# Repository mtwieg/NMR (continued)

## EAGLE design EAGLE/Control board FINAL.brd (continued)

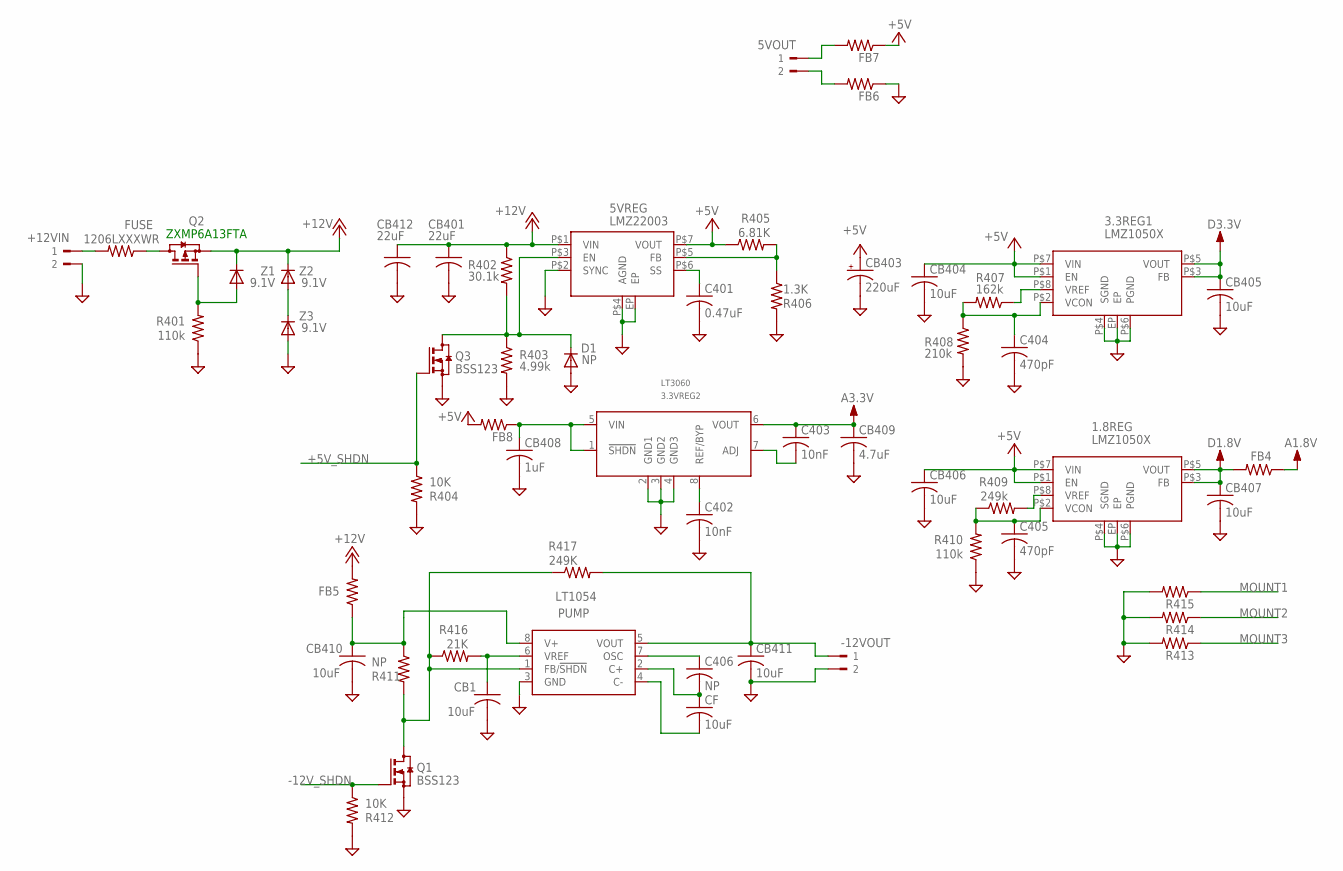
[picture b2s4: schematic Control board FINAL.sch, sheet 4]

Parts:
1.8REG, 3.3REG1: LMZ1050X; LLP-8
3.3VREG2: LT3060; TSOT-8
5VOUT: TERM-2OMNIMATE_SL; OMNIMATE_SL_2POS
5VREG: LMZ22003; TO-PMOD7
+12VIN: TERM-2OMNIMATE_SL; OMNIMATE_SL_2POS
-12VOUT: TERM-2OMNIMATE_SL; OMNIMATE_SL_2POS
C401: 0.47uF; C0805
C402, C403: 10nF; C0603
C404, C405: 470pF; C0603
C406: NP; C0805
CB1, CB404, CB405, CB406, CB407, CB410, CB411: 10uF; C0805
CB401, CB412: 22uF; C1210
CB403: 220uF; E3,5-8
CB408: 1uF; C0805
CB409: 4.7uF; C0805
CF: 10uF; C0805
D1: NP; SOD323-W
FB4: R-US_R0805; R0805
FB5, FB6, FB7, FB8: R-US_R0603; R0603
FUSE: 1206LXXXWR; R1206
PUMP: LT1054; SOIC-8
Q1, Q3: BSS123; SOT23
Q2: ZXMP6A13FTA; SOT23
R401, R410: 110k; R0805
R402: 30.1k; R0805
R403: 4.99k; R0805
R404, R412: 10K; R0805
R405: 6.81K; R0805
R406: 1.3K; R0805
R407: 162k; R0805
R408: 210k; R0805
R409: 249k; R0805
R411: NP; R0805
R413, R414, R415: R-US_R0805; R0805
R416: 21K; R0805
R417: 249K; R0805
Z1: 9.1V; SOD123
Z2, Z3: 9.1V; DO214AC

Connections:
+5V: 1.8REG.P$1 (EN), 1.8REG.P$7 (VIN), 3.3REG1.P$1 (EN), 3.3REG1.P$7 (VIN), 5VREG.P$7 (VOUT), CB403.+, CB404.1, CB406.1, FB7.1, FB8.2, R405.1; also elsewhere on the board
+5V_SHDN: Q3.1 (G), R404.1; also elsewhere on the board
+12V: 5VREG.P$1 (VIN), CB401.1, CB412.1, FB5.2, Q2.2 (S), R402.1, Z1.C, Z2.C
-12V_SHDN: Q1.1 (G), R412.1; also elsewhere on the board
A1.8V: FB4.1; also elsewhere on the board
A3.3V: 3.3VREG2.6 (VOUT), C403.1, CB409.1; also elsewhere on the board
D1.8V: 1.8REG.P$3 (FB), 1.8REG.P$5 (VOUT), CB407.1, FB4.2; also elsewhere on the board
D3.3V: 3.3REG1.P$3 (FB), 3.3REG1.P$5 (VOUT), CB405.1; also elsewhere on the board
GND: 1.8REG.EP, 1.8REG.P$4 (SGND), 1.8REG.P$6 (PGND), 3.3REG1.EP, 3.3REG1.P$4 (SGND), 3.3REG1.P$6 (PGND), 3.3VREG2.2 (GND1), 3.3VREG2.3 (GND2), 3.3VREG2.4 (GND3), 5VREG.EP, 5VREG.P$2 (SYNC), 5VREG.P$4 (AGND), +12VIN.2, -12VOUT.2, C401.2, C402.2, C404.2, C405.2, CB1.2, CB401.2, CB403.-, CB404.2, CB405.2, CB406.2, CB407.2, CB408.2, CB409.2, CB410.2, CB411.2, CB412.2, D1.A, FB6.1, PUMP.3 (GND), Q1.2 (S), Q3.2 (S), R401.1, R403.2, R404.2, R406.2, R408.2, R410.1, R412.2, R413.2, R414.2, R415.2, Z3.A; also elsewhere on the board
MOUNT1: R415.1
MOUNT2: R414.1
MOUNT3: R413.1
unnamed: 5VREG.P$6 (SS), C401.1
unnamed: 5VREG.P$3 (EN), D1.C, Q3.3 (D), R402.2, R403.1
unnamed: 5VOUT.1, FB7.2
unnamed: 5VOUT.2, FB6.2
unnamed: C406.1, PUMP.7 (OSC)
unnamed: C406.2, CF.1, PUMP.2 (C+)
unnamed: 5VREG.P$5 (FB), R405.2, R406.1
unnamed: CB410.1, FB5.1, PUMP.8 (V+), R411.1
unnamed: 3.3REG1.P$2 (VCON), C404.1, R407.2, R408.1
unnamed: 3.3REG1.P$8 (VREF), R407.1
unnamed: 1.8REG.P$8 (VREF), R409.2
unnamed: 1.8REG.P$2 (VCON), C405.1, R409.1, R410.2
unnamed: CB1.1, PUMP.6 (VREF), R416.2
unnamed: 3.3VREG2.8 (REF/BYP), C402.1
unnamed: 3.3VREG2.7 (ADJ), C403.2
unnamed: +12VIN.1, FUSE.2
unnamed: Q2.1 (G), R401.2, Z1.A
unnamed: FUSE.1, Q2.3 (D)
unnamed: -12VOUT.1, CB411.1, PUMP.5 (VOUT), R417.2
unnamed: CF.2, PUMP.4 (C-)
unnamed: Z2.A, Z3.C
unnamed: 3.3VREG2.1 (!SHDN), 3.3VREG2.5 (VIN), CB408.1, FB8.1
unnamed: PUMP.1 (FB/!SHDN), Q1.3 (D), R411.2, R416.1, R417.1

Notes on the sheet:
ZXMP6A13FTA

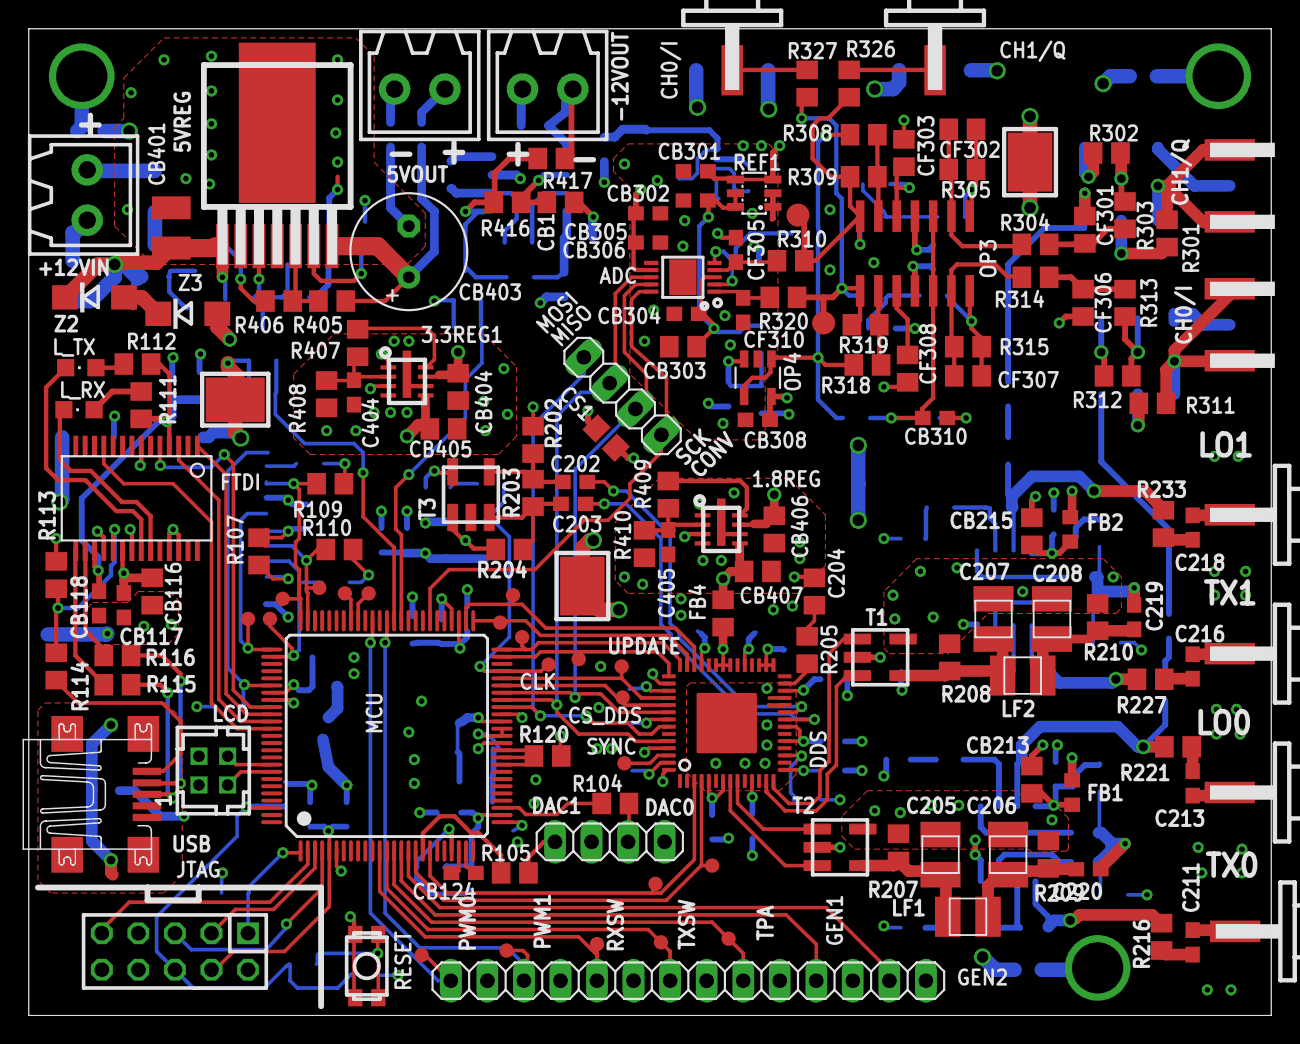
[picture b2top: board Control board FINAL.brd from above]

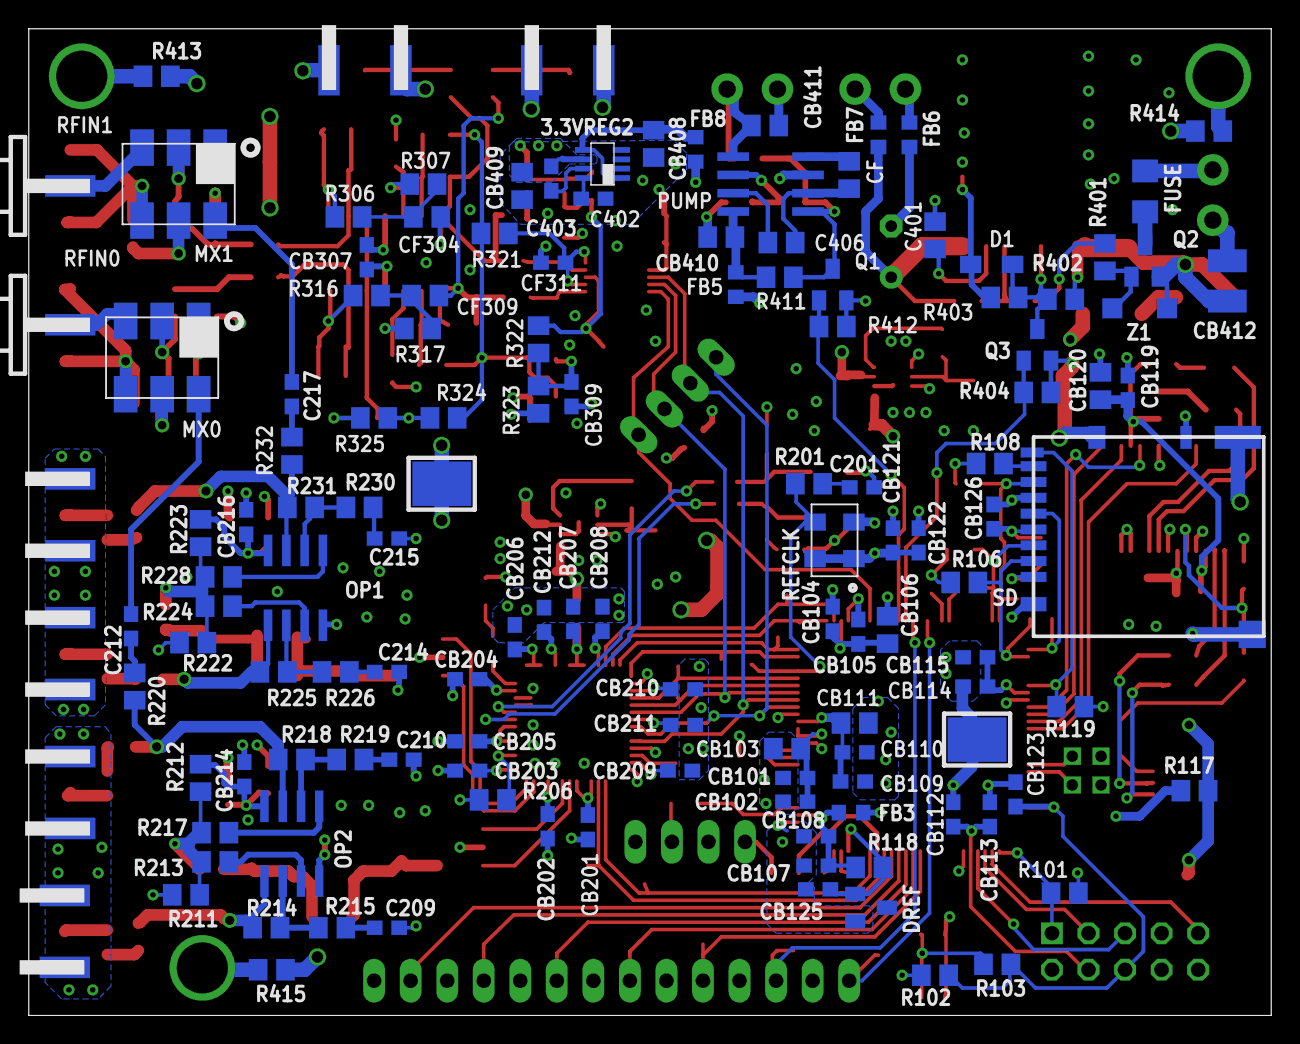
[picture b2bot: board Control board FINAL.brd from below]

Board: 4 copper layers, 86.4 x 68.6 mm, 287 parts (128 on the bottom side), 174 nets.

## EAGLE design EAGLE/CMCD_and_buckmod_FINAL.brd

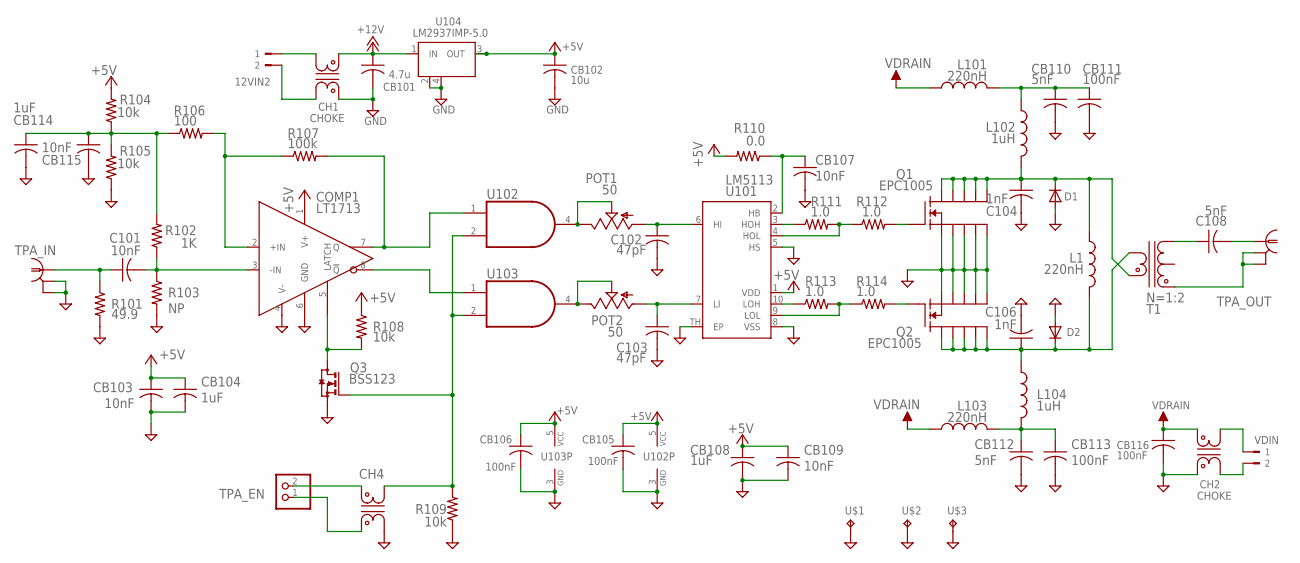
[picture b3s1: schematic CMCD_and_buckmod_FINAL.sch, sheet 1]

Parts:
12VIN2: TERM-2OMNIMATE_SL; OMNIMATE_SL_2POS
C101: 10nF; C0805
C102, C103: 47pF; C0805
C104, C106: 1nF; 1008
C108: 5nF; 1008
CB101: 4.7u; C0805
CB102: 10u; C0805
CB103, CB107, CB109, CB115: 10nF; C0603
CB104, CB108: 1uF; C0603
CB105, CB106: 100nF; C0603
CB110, CB112: 5nF; 1008
CB111, CB113, CB116: 100nF; C0805
CB114: 1uF; C0805
CH1, CH2: CHOKE; CHOKE_DLW5BT
CH4: CHOKEDLW31S; CHOKE_DLW31S
COMP1: LT1713; MSOP-8
D1, D2: DIODE-DO214AC; DO214AC
L1, L101, L103: 220nH; GENERAL-1
L102, L104: 1uH; GENERAL-1
POT1, POT2: 50; 3223W
Q1, Q2: EPC1005; 11-LGA
Q3: BSS123; SOT23
R101: 49.9; R0805
R102: 1K; R0805
R103: NP; R0805
R104, R105, R108, R109: 10k; R0805
R106: 100; R0805
R107: 100k; R0805
R110: 0.0; R0603
R111, R112, R113, R114: 1.0; R0603
T1: N=1:2; BALUN_GENERAL_BIG
TPA_EN: PINHD-1X2; 1X02
TPA_IN: BNC-EDGE
TPA_OUT: BNC-EDGE
U101: LM5113; LLP-10
U102, U103: 74AHC1G08DBV; SOT23-5
U104: LM2937IMP-5.0; SOT223
U$1, U$2, U$3: TESTPOINTKEYSTONE_ELECTRONICS_5016; SMD_TESTPAD
VDIN: TERM-2OMNIMATE_SL; OMNIMATE_SL_2POS

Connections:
+5V: CB102.1, CB103.1, CB104.1, CB105.1, CB106.1, CB108.1, CB109.1, COMP1.1 (V+), R104.2, R108.1, R110.2, U101.1 (VDD), U102.5 (VCC), U103.5 (VCC), U104.3 (OUT); also elsewhere on the board
+12V: CB101.1, CH1.P$4 (4), U104.1 (IN); also elsewhere on the board
GND: C102.2, C103.2, C104.P$2 (2), C106.P$2 (2), CB101.2, CB102.2, CB103.2, CB104.2, CB105.2, CB106.2, CB107.2, CB108.2, CB109.2, CB110.P$2 (2), CB111.2, CB112.P$2 (2), CB113.2, CB114.2, CB115.2, CB116.2, CH1.P$1 (1), CH2.P$1 (1), CH4.P$2 (2), COMP1.4 (V-), COMP1.6 (GND), D1.A, D2.A, Q1.2 (S1), Q1.4 (S2), Q1.6 (S3), Q1.8 (S4), Q1.10 (S5), Q2.2 (S1), Q2.4 (S2), Q2.6 (S3), Q2.8 (S4), Q2.10 (S5), Q3.2 (S), R101.2, R103.2, R105.1, R109.1, TPA_IN.S1 (GND1), TPA_IN.S2 (GND2), U101.5 (HS), U101.8 (VSS), U101.TH (EP), U102.3 (GND), U103.3 (GND), U104.2 (GND), U104.4 (GND), U$1.P$1, U$2.P$1, U$3.P$1; also elsewhere on the board
unnamed: R111.1, U101.3 (HOH)
unnamed: R111.2, R112.1, U101.4 (HOL)
unnamed: R113.1, U101.10 (LOH)
unnamed: R113.2, R114.1, U101.9 (LOL)
unnamed: Q2.1 (G), R114.2
unnamed: Q1.1 (G), R112.2
unnamed: CB107.1, R110.1, U101.2 (HB)
unnamed: COMP1.7 (Q), R107.2, U102.1 (I0)
unnamed: POT1.2 (S), POT1.3 (E), U102.4 (O)
unnamed: POT2.2 (S), POT2.3 (E), U103.4 (O)
unnamed: CB114.1, CB115.1, R102.2, R104.1, R105.2, R106.1
unnamed: COMP1.8 (!Q), U103.1 (I0)
unnamed: COMP1.5 (LATCH), Q3.3 (D), R108.2
unnamed: T1.S1 (6), TPA_OUT.S1 (GND1), TPA_OUT.S2 (GND2)
unnamed: C102.1, POT1.1 (A), U101.6 (HI)
unnamed: COMP1.2 (+IN), R106.2, R107.1
unnamed: C101.2, COMP1.3 (-IN), R102.1, R103.1
unnamed: C101.1, R101.1, TPA_IN.I (1)
unnamed: CH4.P$3 (3), Q3.1 (G), R109.2, U102.2 (I1), U103.2 (I1)
unnamed: CH2.P$3 (3), VDIN.1
unnamed: CH2.P$2 (2), VDIN.2
unnamed: C106.P$1 (1), D2.C, L1.P$2 (2), L104.P$1 (1), Q2.3 (D1), Q2.5 (D2), Q2.7 (D3), Q2.9 (D4), Q2.11 (D5), T1.P2 (3)
unnamed: C103.1, POT2.1 (A), U101.7 (LI)
unnamed: C104.P$1 (1), D1.C, L1.P$1 (1), L102.P$2 (2), Q1.3 (D1), Q1.5 (D2), Q1.7 (D3), Q1.9 (D4), Q1.11 (D5), T1.P1 (1)
unnamed: CB110.P$1 (1), CB111.1, L101.P$2 (2), L102.P$1 (1)
unnamed: CB112.P$1 (1), CB113.1, L103.P$2 (2), L104.P$2 (2)
unnamed: C108.P$2 (2), TPA_OUT.I (1)
unnamed: C108.P$1 (1), T1.S2 (4)
unnamed: 12VIN2.1, CH1.P$3 (3)
unnamed: 12VIN2.2, CH1.P$2 (2)
unnamed: CH4.P$4 (4), TPA_EN.2
unnamed: CH4.P$1 (1), TPA_EN.1
VDRAIN: CB116.1, CH2.P$4 (4), L101.P$1 (1), L103.P$1 (1)

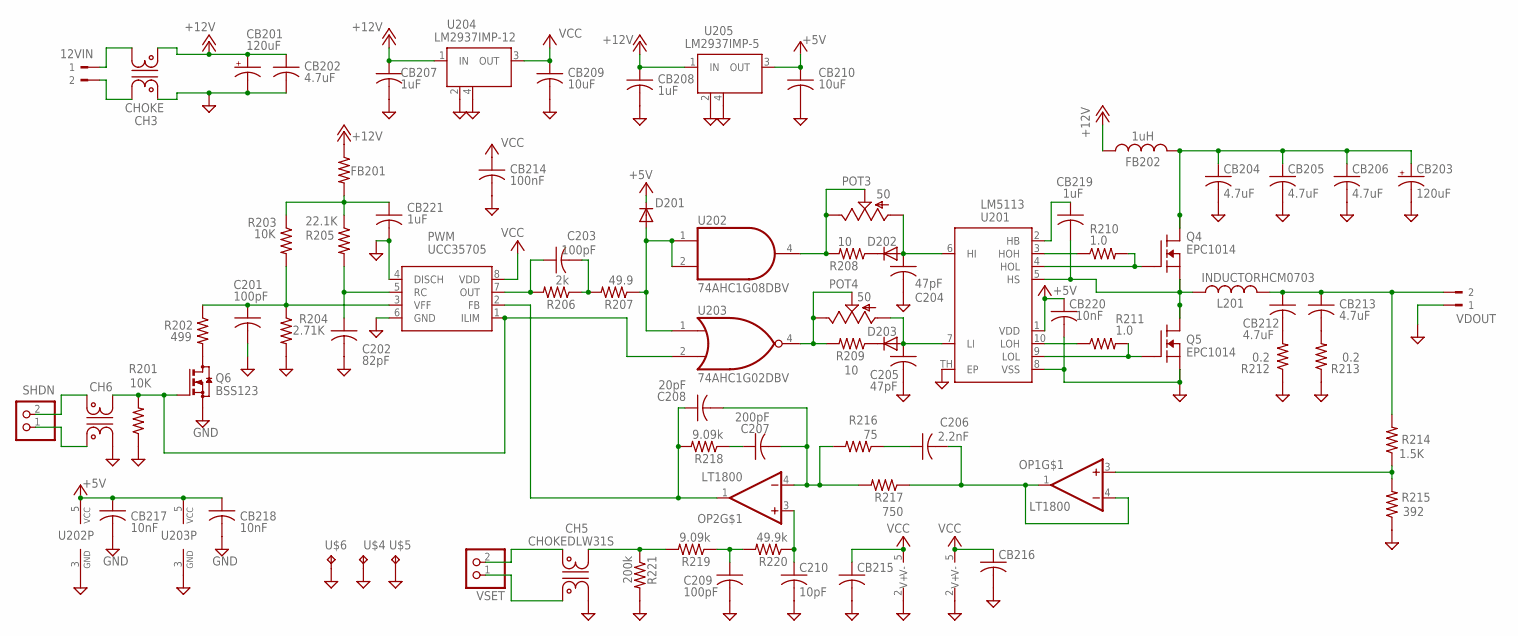
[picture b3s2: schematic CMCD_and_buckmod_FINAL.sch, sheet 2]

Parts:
12VIN: TERM-2OMNIMATE_SL; OMNIMATE_SL_2POS
C201, C203, C209: 100pF; C0805
C202: 82pF; C0805
C204, C205: 47pF; C0603
C206: 2.2nF; C0805
C207: 200pF; C0805
C208: 20pF; C0805
C210: 10pF; C0805
CB201, CB203: 120uF; E3,5-8
CB202, CB204, CB212, CB213: 4.7uF; C0805
CB205, CB206: 4.7uF; 1206-LONG
CB207, CB208, CB221: 1uF; C0805
CB209, CB210: 10uF; C0805
CB214: 100nF; C0603
CB215, CB216: C-USC0603; C0603
CB217, CB218, CB220: 10nF; C0603
CB219: 1uF; C0603
CH3: CHOKE; CHOKE_DLW5BT
CH5, CH6: CHOKEDLW31S; CHOKE_DLW31S
D201, D202, D203: DIODE-SOD323-W; SOD323-W
FB201: R-US_R0805; R0805
FB202: 1uH; 1008
L201: INDUCTORHCM0703; HCM0703
OP1, OP2: LT1800; SOT23-5
POT3, POT4: 50; 3223W
PWM: UCC35705; MSOP-8
Q4, Q5: EPC1014; 5-LGA
Q6: BSS123; SOT23
R201, R203: 10K; R0805
R202: 499; R0805
R204: 2.71K; R0805
R205: 22.1K; R0805
R206: 2k; R0805
R207: 49.9; R0805
R208, R209: 10; R0805
R210, R211: 1.0; R0603
R212, R213: 0.2; R0805
R214: 1.5K; R0805
R215: 392; R0805
R216: 75; R0805
R217: 750; R0805
R218, R219: 9.09k; R0805
R220: 49.9k; R0805
R221: 200k; R0805
SHDN: PINHD-1X2; 1X02
U201: LM5113; LLP-10
U202: 74AHC1G08DBV; SOT23-5
U203: 74AHC1G02DBV; SOT23-5
U204: LM2937IMP-12; SOT223
U205: LM2937IMP-5; SOT223
U$4, U$5, U$6: TESTPOINTKEYSTONE_ELECTRONICS_5016; SMD_TESTPAD
VDOUT: TERM-2OMNIMATE_SL; OMNIMATE_SL_2POS
VSET: PINHD-1X2; 1X02

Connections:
+5V: CB210.1, CB217.1, CB218.1, CB220.1, D201.C, U201.1 (VDD), U202.5 (VCC), U203.5 (VCC), U205.3 (OUT); also elsewhere on the board
+12V: CB201.+, CB202.1, CB207.1, CB208.1, CH3.P$4 (4), FB201.1, FB202.P$1 (1), U204.1 (IN), U205.1 (IN); also elsewhere on the board
+VIN: CB203.+, CB204.1, CB205.1, CB206.1, FB202.P$2 (2), Q4.3 (D), Q4.5 (D1)
GND: C201.2, C202.2, C204.2, C205.2, C209.2, C210.2, CB201.-, CB202.2, CB203.-, CB204.2, CB205.2, CB206.2, CB207.2, CB208.2, CB209.2, CB210.2, CB214.2, CB215.2, CB216.2, CB217.2, CB218.2, CB220.2, CB221.2, CH3.P$1 (1), CH5.P$2 (2), CH6.P$2 (2), OP1.2 (V-), OP2.2 (V-), PWM.4 (DISCH), PWM.6 (GND), Q5.2 (S1), Q5.4 (S2), Q6.2 (S), R201.1, R204.2, R212.1, R213.1, R215.1, R221.2, U201.8 (VSS), U201.TH (EP), U202.3 (GND), U203.3 (GND), U204.2 (GND), U204.4 (GND), U205.2 (GND), U205.4 (GND), U$4.P$1, U$5.P$1, U$6.P$1, VDOUT.1; also elsewhere on the board
unnamed: 12VIN.2, CH3.P$2 (2)
unnamed: 12VIN.1, CH3.P$3 (3)
unnamed: R210.1, U201.3 (HOH)
unnamed: Q4.1 (G), R210.2, U201.4 (HOL)
unnamed: CH5.P$4 (4), VSET.2
unnamed: CH5.P$1 (1), VSET.1
unnamed: CH6.P$4 (4), SHDN.2
unnamed: CH6.P$1 (1), SHDN.1
unnamed: R211.1, U201.10 (LOH)
unnamed: Q5.1 (G), R211.2, U201.9 (LOL)
unnamed: CB219.2, L201.P$1 (1), Q4.2 (S1), Q4.4 (S2), Q5.3 (D), Q5.5 (D1), U201.5 (HS)
unnamed: C205.1, D203.A, POT4.1 (A), U201.7 (LI)
unnamed: C204.1, D202.A, POT3.1 (A), U201.6 (HI)
unnamed: POT4.2 (S), POT4.3 (E), R209.2, U203.4 (O)
unnamed: CB219.1, U201.2 (HB)
unnamed: C208.1, OP2.1 (OUT), PWM.2 (FB), R218.2
unnamed: C207.2, C208.2, OP2.4 (-IN), R216.2, R217.2
unnamed: C207.1, R218.1
unnamed: C206.1, R216.1
unnamed: C206.2, OP1.1 (OUT), OP1.4 (-IN), R217.1
unnamed: CB213.2, R213.2
unnamed: CB212.1, CB213.1, L201.P$2 (2), R214.2, VDOUT.2
unnamed: OP1.3 (+IN), R214.1, R215.2
unnamed: C209.1, R219.1, R220.2
unnamed: CB212.2, R212.2
unnamed: CH5.P$3 (3), R219.2, R221.1
unnamed: D201.A, R207.1, U202.1 (I0), U202.2 (I1), U203.1 (I0)
unnamed: C202.1, PWM.5 (RC), R205.2
unnamed: C201.1, PWM.3 (VFF), R202.1, R203.2, R204.1
unnamed: C203.1, PWM.7 (OUT), R206.2
unnamed: C203.2, R206.1, R207.2
unnamed: Q6.3 (D), R202.2
unnamed: CB221.1, FB201.2, R203.1, R205.1
unnamed: D203.C, R209.1
unnamed: D202.C, R208.1
unnamed: POT3.2 (S), POT3.3 (E), R208.2, U202.4 (O)
unnamed: CH6.P$3 (3), PWM.1 (ILIM), Q6.1 (G), R201.2, U203.2 (I1)
OP2: C210.1, OP2.3 (+IN), R220.1
VCC: CB209.1, CB214.1, CB215.1, CB216.1, OP1.5 (V+), OP2.5 (V+), PWM.8 (VDD), U204.3 (OUT)

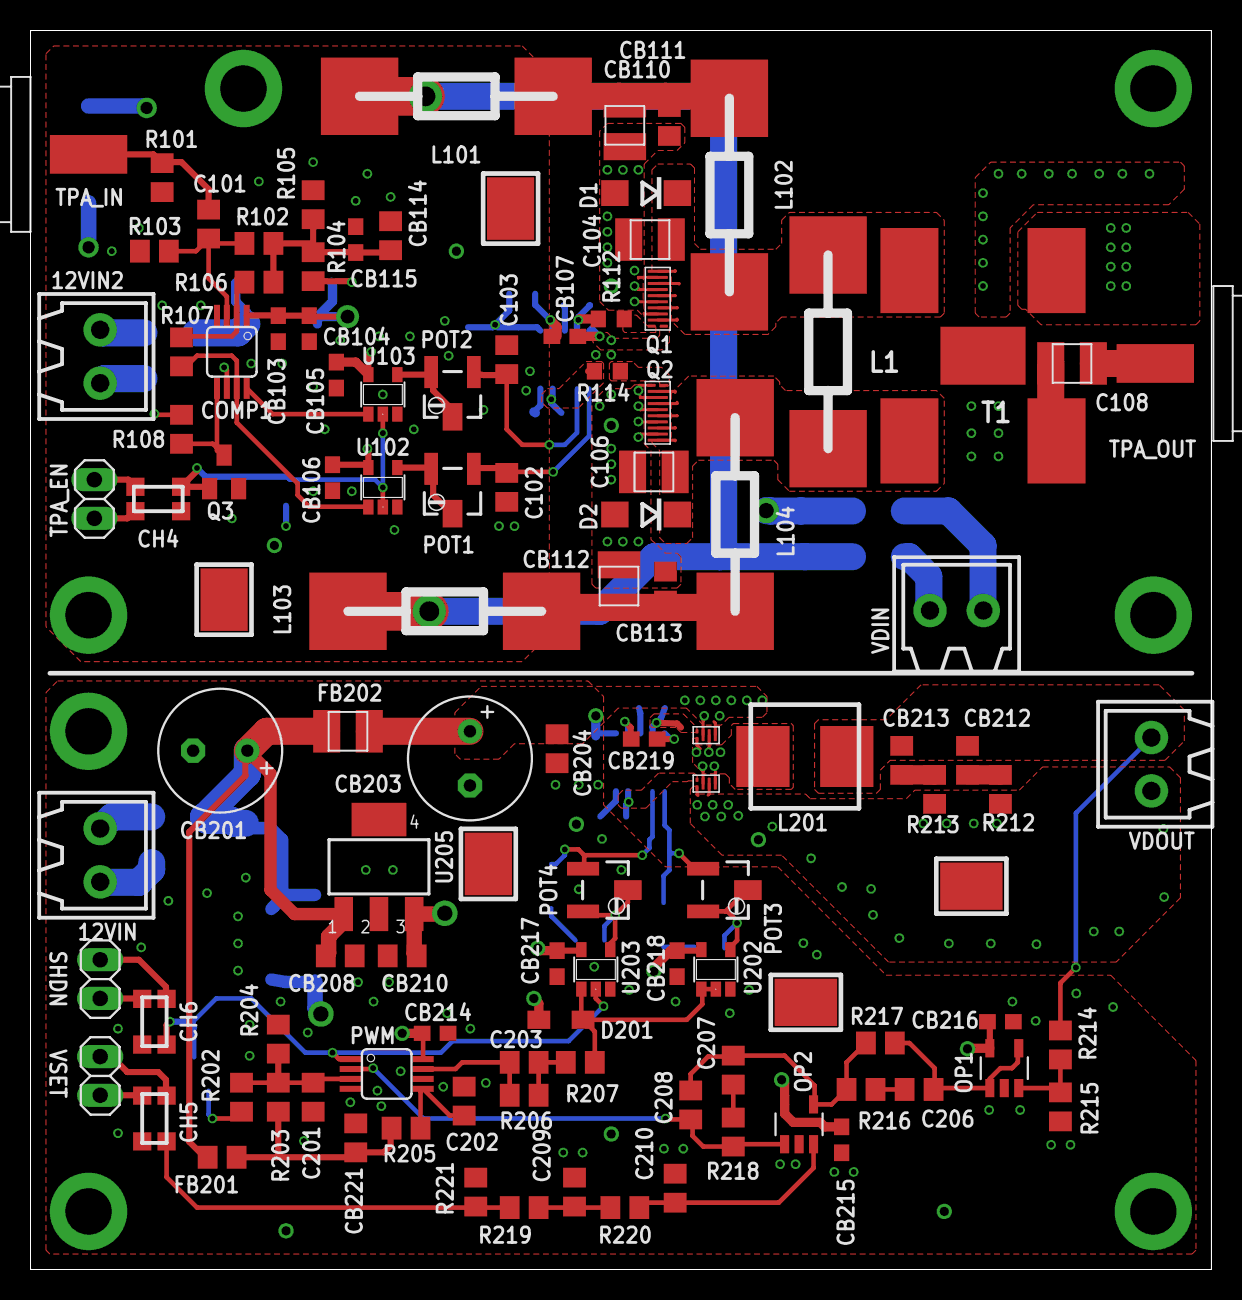
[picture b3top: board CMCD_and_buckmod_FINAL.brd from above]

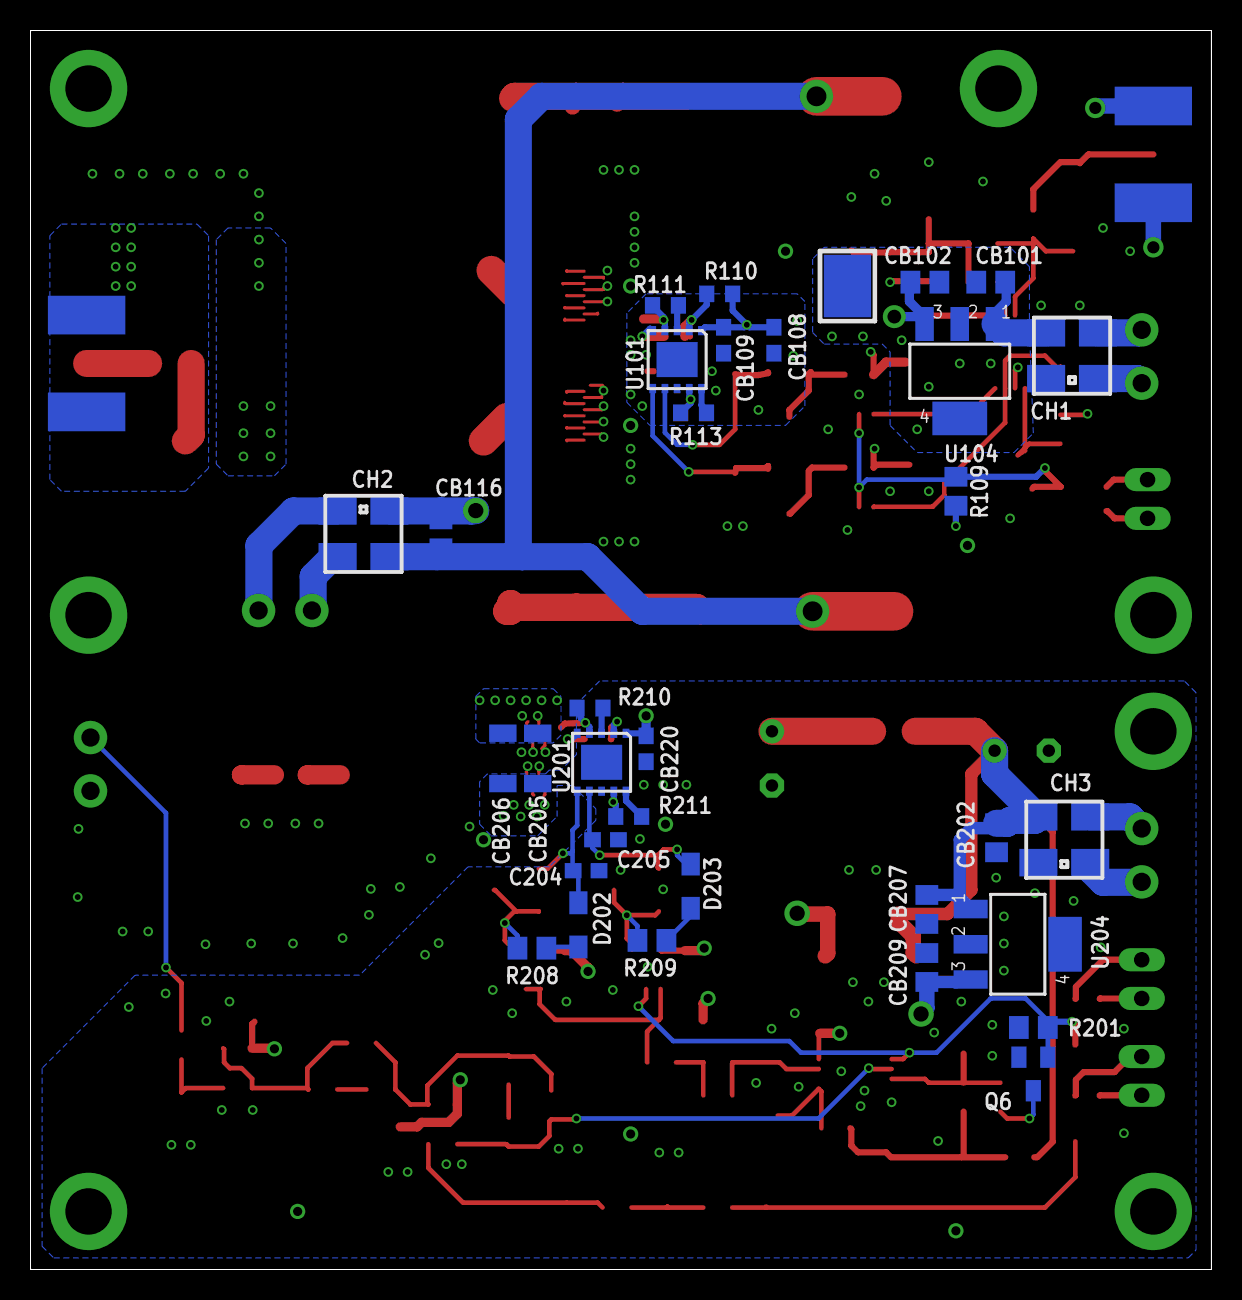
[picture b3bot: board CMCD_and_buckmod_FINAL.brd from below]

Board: 4 copper layers, 77.5 x 81.3 mm, 145 parts (33 on the bottom side), 76 nets.

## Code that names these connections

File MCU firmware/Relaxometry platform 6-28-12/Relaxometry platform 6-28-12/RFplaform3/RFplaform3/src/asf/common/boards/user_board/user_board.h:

/**
 * \file
 *
 * \brief User board definition template
 *
 */

#  define USB_USART                 (&AVR32_USART1)			//USB USART assignments third version of RF platform
#  define USB_USART_TX_PDCA_PID		AVR32_PDCA_PID_USART1_TX
#  define USB_USART_RX_PDCA_PID		AVR32_PDCA_PID_USART1_RX
#  define USB_USART_RX_PIN          AVR32_USART1_RXD_0_1_PIN	//PD12
#  define USB_USART_RX_FUNCTION     AVR32_USART1_RXD_0_1_FUNCTION	//
#  define USB_USART_TX_PIN          AVR32_USART1_TXD_0_1_PIN		//PD11
#  define USB_USART_TX_FUNCTION     AVR32_USART1_TXD_0_1_FUNCTION	//
#  define USB_USART_CTS_PIN          AVR32_USART1_CTS_0_1_PIN		//PD11
#  define USB_USART_CTS_FUNCTION     AVR32_USART1_CTS_0_1_FUNCTION	//
#  define USB_USART_RTS_PIN          AVR32_USART1_RTS_0_1_PIN		//PD11
#  define USB_USART_RTS_FUNCTION     AVR32_USART1_RTS_0_1_FUNCTION	//

#  define LCD_USART                 (&AVR32_USART0)			//USART for communicating with LCD
#  define LCD_USART_RX_PDCA_PID		AVR32_PDCA_PID_USART0_RX
#  define LCD_USART_RX_PIN          AVR32_USART0_RXD_0_0_PIN	//PD28
#  define LCD_USART_RX_FUNCTION     AVR32_USART0_RXD_0_0_FUNCTION  //
#  define LCD_USART_TX_PIN          AVR32_USART0_TXD_0_0_PIN		//PD27
#  define LCD_USART_TX_FUNCTION     AVR32_USART0_TXD_0_0_FUNCTION	//

#  define SPI1					    (&AVR32_SPI1)				//THESE ARE SPI ASSIGNMENTS FOR EVK HACK
#  define SPI1_RX_PDCA_PID				AVR32_PDCA_PID_SPI1_RX
#  define SPI1_NPCS2_PIN				AVR32_SPI1_NPCS_3_2_PIN 		//PAB23 is DDS CS
#  define SPI1_NPCS2_FUNCTION			AVR32_SPI1_NPCS_3_2_FUNCTION
#  define SPI1_MISO_PIN				AVR32_SPI1_MISO_0_1_PIN		//PB20
#  define SPI1_MISO_FUNCTION			AVR32_SPI1_MISO_0_1_FUNCTION
#  define SPI1_MOSI_PIN				AVR32_SPI1_MOSI_0_1_PIN		//PB19
#  define SPI1_MOSI_FUNCTION			AVR32_SPI1_MOSI_0_1_FUNCTION
#  define SPI1_SCK_PIN				AVR32_SPI1_SCK_0_1_PIN 		//PB21
#  define SPI1_SCK_FUNCTION			AVR32_SPI1_SCK_0_1_FUNCTION

#  define SPI0						   (&AVR32_SPI0)				//THESE ARE SPI ASSIGNMENTS FOR EVK HACK
#  define SPI0_TX_PDCA_PID			AVR32_PDCA_PID_SPI0_TX
#  define SPI0_RX_PDCA_PID			AVR32_PDCA_PID_SPI0_RX
#  define SD_MMC_SPI					(&AVR32_SPI0)
#  define SD_MMC_SPI_NPCS				0
#  define SPI0_RX_PDCA_PID				AVR32_PDCA_PID_SPI0_RX
#  define SPI0_NPCS0_PIN				AVR32_SPI0_NPCS_0_0_PIN		//PD03 is NPCS0, CS for SD card
#  define SPI0_NPCS0_FUNCTION			AVR32_SPI0_NPCS_0_0_FUNCTION
#  define SPI0_MISO_PIN				AVR32_SPI0_MISO_0_0_PIN		//PD01
#  define SPI0_MISO_FUNCTION			AVR32_SPI0_MISO_0_0_FUNCTION
#  define SPI0_MOSI_PIN				AVR32_SPI0_MOSI_0_0_PIN  	//PD00
#  define SPI0_MOSI_FUNCTION			AVR32_SPI0_MOSI_0_0_FUNCTION
#  define SPI0_SCK_PIN				AVR32_SPI0_SCK_0_0_PIN 		//PD02
#  define SPI0_SCK_FUNCTION			AVR32_SPI0_SCK_0_0_FUNCTION

//GPIO assignments for RF platform 3
#  define ADC_CONV_pin					AVR32_PIN_PC06	
#  define DDS_IOUD_pin					AVR32_PIN_PB23
#  define DDS_RESET_pin					AVR32_PIN_PA13
#  define DDS_PDN_pin					AVR32_PIN_PA11
#  define DDS_P0_pin					AVR32_PIN_PC03
#  define DDS_P1_pin					AVR32_PIN_PC02
#  define DDS_P2_pin					AVR32_PIN_PC01
#  define DDS_P3_pin					AVR32_PIN_PC00

#  define TPAbias_pin					AVR32_PIN_PA08
#  define TXSW_pin						AVR32_PIN_PA07
#  define RXSW_pin						AVR32_PIN_PA06
#  define PWM0_pin						AVR32_PIN_PC17
#  define PWM1_pin						AVR32_PIN_PC15
#  define GEN1_pin						AVR32_PIN_PA09
#  define GEN2_pin						AVR32_PIN_PA10
#  define SD_detect_pin					AVR32_PIN_PD10

#  define DAC0					(&AVR32_DACIFB0)
#  define DAC1					(&AVR32_DACIFB1)
#  define DAC0A_pin				AVR32_DAC0A_PIN  	//PD00
#  define DAC0A_FUNCTION			AVR32_DAC0A_FUNCTION
#  define DAC1A_pin				AVR32_DAC1A_PIN  	//PD00
#  define DAC1A_FUNCTION			AVR32_DAC1A_FUNCTION

# define DAC_PRESCALER_CLK	7500000

#define DDS_PCS 7
#define ADC_PCS 14

#define FAST_TC				(&AVR32_TC0)
#define FAST_TC_CHANNEL		0
#define SLOW_TC				(&AVR32_TC1)
#define SLOW_TC_fast_CHANNEL		1
#define SLOW_TC_slow_CHANNEL		0

#define TC1_TCIOA1_pin			AVR32_PIN_PB02

#define OSC0_STARTUP    0	//for external oscillator
#define FOSC0       20000000
#define CPU_SPEED   60000000
#define PBA_SPEED   60000000

#define desired_DDS_Fs 300000000
#if (desired_DDS_Fs>500000000 || (desired_DDS_Fs>160000000 && desired_DDS_Fs < 255000000))
#error "Specified Fs is out of range"
#endif

#define DDS_PLL_div (desired_DDS_Fs/FOSC0)
#if (DDS_PLL_div<4 || DDS_PLL_div>20)
#error "DDS PLL multiplication factor out of range"
#endif

#define DDS_Fs (FOSC0*DDS_PLL_div)
#if (DDS_Fs>500000000 || (DDS_Fs>160000000 && DDS_Fs < 255000000))
#error "Actual Fs is out of range"
#endif

#if DDS_Fs<=160000000
#define DDS_VCO_gain 0
#else
#define DDS_VCO_gain 1
#endif

#define SD_SPI_SPEED 20000000
#define DDS_SPI		(&AVR32_SPI1)

#define SPI1_RX_PDCA_CHANNEL 0
#define SPI0_RX_PDCA_CHANNEL 1
#define SPI0_TX_PDCA_CHANNEL 2
#define USB_USART_TX_PDCA_CHANNEL 3
#define USB_USART_RX_PDCA_CHANNEL 4
#define LCD_USART_RX_PDCA_CHANNEL 5

#define MY_PDCA					    (&AVR32_PDCA)				//THESE ARE SPI ASSIGNMENTS FOR EVK HACK

#  define EXAMPLE_TARGET_PBACLK_FREQ_HZ FOSC0  // PBA clock target frequency, in Hz

#ifndef USER_BOARD_H
#define USER_BOARD_H

#endif // USER_BOARD_H

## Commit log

2013-04-18 Uploaded boms
2013-04-18 Uploaded all matlab files
2013-04-18 Uploaded Atmel Studio project directory for MCU firmware.
2013-04-18 Uploaded EAGLE design files
2013-04-18 Uploaded ezLCD-301 macros
2013-04-18 Fixed minor bug in Toplevel.c Some LCD commands were being sent to USB.
2013-04-18 Uploaded thesis
2013-04-29 Update README.md
    Post-ISMRM thoughts about future directions
2023-05-04 add LICENSE notice according to REUSE spec
2023-05-04 add hardware license
2023-05-04 add software license
2023-05-04 add cc license
2023-05-04 add license notice in README
2023-05-04 pretify license text
